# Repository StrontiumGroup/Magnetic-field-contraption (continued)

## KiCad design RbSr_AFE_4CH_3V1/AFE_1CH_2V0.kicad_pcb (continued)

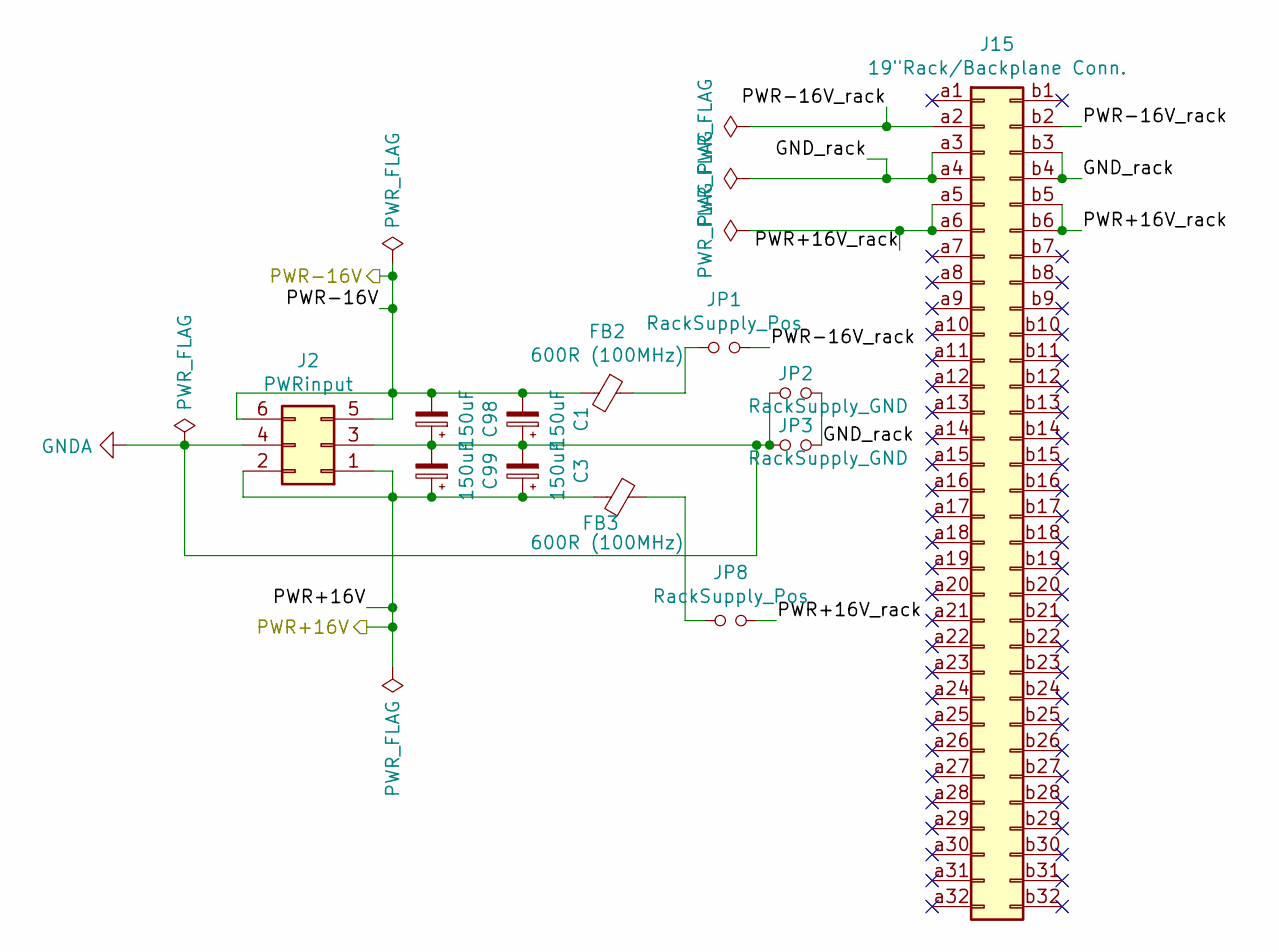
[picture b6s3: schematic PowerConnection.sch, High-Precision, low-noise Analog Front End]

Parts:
C1, C3, C98, C99: 150uF; CP_Elec_6.3x5.8; DigiKey 565-APXJ200ARA151MF61GCT-ND
FB2, FB3: 600R (100MHz); L_0603_1608Metric; DigiKey MH1608-601YCT-ND
J2: PWRinput; IDC-Header_2x03_P2.54mm_Vertical; DigiKey 609-5122-ND
J15: 19\"Rack/Backplane Conn.; Socket_DIN41612-CaseC1-AC-Male-64Pin-2rows; DigiKey 1195-1143-ND
JP1: RackSupply_Pos; PinHeader_1x02_P1.27mm_Vertical; DigiKey 732-5315-ND
JP2, JP3: RackSupply_GND; PinHeader_1x02_P1.27mm_Vertical; DigiKey 732-5315-ND
JP8: RackSupply_Pos; PinHeader_1x02_P1.27mm_Vertical; DigiKey 61300211121

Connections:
/PWR+16V: C3.1, C99.1, FB3.1, J2.1, J2.2; also elsewhere on the board
/PWR-16V: C1.2, C98.2, FB2.2, J2.5, J2.6; also elsewhere on the board
/PowerCconnection1/GND_rack: J15.a3, J15.a4, J15.b3, J15.b4, JP2.2, JP3.2
/PowerCconnection1/PWR+16V_rack: J15.a5, J15.a6, J15.b5, J15.b6, JP8.2
/PowerCconnection1/PWR-16V_rack: J15.a2, J15.b2, JP1.2
GND: C1.1, C3.2, C98.1, C99.2, J2.3, J2.4, JP2.1, JP3.1; also elsewhere on the board
unnamed: FB2.1, JP1.1
unnamed: FB3.2, JP8.1

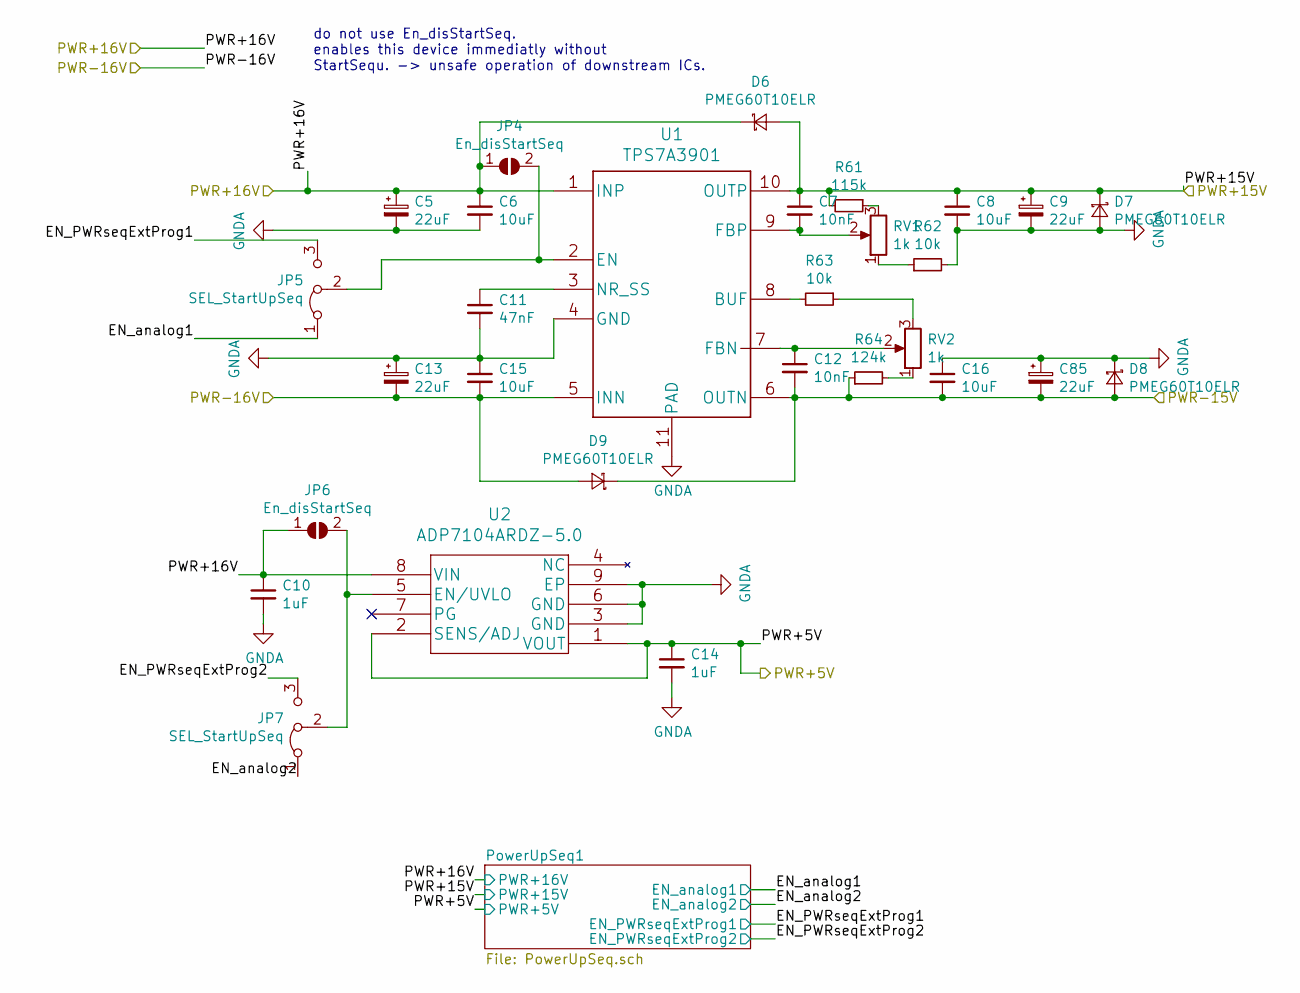
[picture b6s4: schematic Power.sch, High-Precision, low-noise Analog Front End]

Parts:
C5, C9, C13, C85: 22uF; CP_Elec_6.3x5.7; DigiKey 399-A767EB226M1VLAE050CT-ND
C6, C8, C15, C16: 10uF; C_1210_3225Metric; DigiKey 445-4536-1-ND
C7, C12: 10nF; R_0603_1608Metric; DigiKey 490-9666-1-ND
C10, C14: 1uF; C_0805_2012Metric; DigiKey 1276-1029-1-ND
C11: 47nF; C_0603_1608Metric; DigiKey 311-1427-1-ND
D6, D7, D8, D9: PMEG60T10ELR; D_SOD-123; DigiKey 1727-7807-1-ND
JP4, JP6: En_disStartSeq; SolderJumper-2_P1.3mm_Open_TrianglePad1.0x1.5mm
JP5, JP7: SEL_StartUpSeq; SolderJumper-3_P2.0mm_Open_TrianglePad1.0x1.5mm_NumberLabels
R61: 115k; R_0603_1608Metric; DigiKey 311-115KHRCT-ND
R62, R63: 10k; R_0805_2012Metric; DigiKey 311-10.0KCRCT-ND
R64: 124k; R_0603_1608Metric; DigiKey 311-124KHRCT-ND
RV1, RV2: 1k; Potentiometer_Bourns_3314G_Vertical; DigiKey 3314G-102ECT-ND
U1: TPS7A3901; Texas_DSC0010J_ThermalVias; DigiKey 296-47504-1-ND
U2: ADP7104ARDZ-5.0; SOIC-8-1EP_3.9x4.9mm_P1.27mm_EP2.41x3.81mm; DigiKey ADP7104ARDZ-5.0-R7CT-ND

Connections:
/PWR+5V: C14.1, U2.1 (VOUT), U2.2 (SENS/ADJ); also elsewhere on the board
/PWR+15V: C7.1, C8.1, C9.1, D6.2 (A), D7.1 (K), R61.2, U1.10 (OUTP); also elsewhere on the board
/PWR+16V: C5.1, C6.1, C10.1, D6.1 (K), JP4.1 (A), JP6.1 (A), U1.1 (INP), U2.8 (VIN); also elsewhere on the board
/PWR-15V: C12.2, C16.2, C85.2, D8.2 (A), D9.1 (K), R64.1, U1.6 (OUTN); also elsewhere on the board
/PWR-16V: C13.2, C15.2, D9.2 (A), U1.5 (INN); also elsewhere on the board
/Power/EN_PWRseqExtProg1: JP5.3 (B); also elsewhere on the board
/Power/EN_PWRseqExtProg2: JP7.3 (B); also elsewhere on the board
/Power/EN_analog1: JP5.1 (A); also elsewhere on the board
/Power/EN_analog2: JP7.1 (A); also elsewhere on the board
GND: C5.2, C6.2, C8.2, C9.2, C10.2, C11.2, C13.1, C14.2, C15.1, C16.1, C85.1, D7.2 (A), D8.1 (K), R62.2, U1.4 (GND), U1.11 (PAD), U2.3 (GND), U2.6 (GND), U2.9 (EP); also elsewhere on the board
unnamed: C7.2, RV1.2, U1.9 (FBP)
unnamed: C11.1, U1.3 (NR_SS)
unnamed: C12.1, RV2.2, U1.7 (FBN)
unnamed: JP4.2 (B), JP5.2 (C), U1.2 (EN)
unnamed: JP6.2 (B), JP7.2 (C), U2.5 (EN/UVLO)
unnamed: R61.1, RV1.3
unnamed: R62.1, RV1.1
unnamed: R63.1, RV2.3
unnamed: R63.2, U1.8 (BUF)
unnamed: R64.2, RV2.1

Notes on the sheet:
do not use En_disStartSeq. enables this device immediatly without StartSequ. -> unsafe operation of downstream ICs.

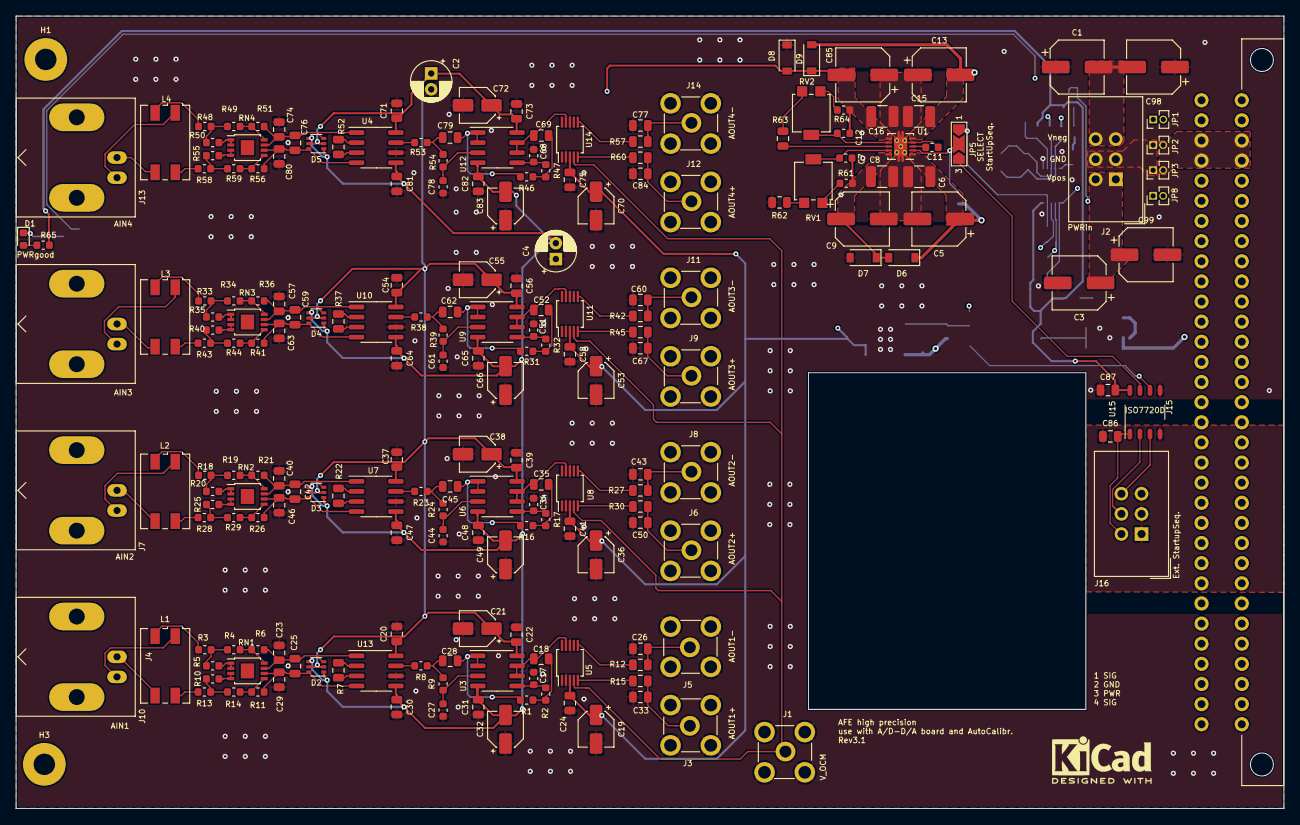
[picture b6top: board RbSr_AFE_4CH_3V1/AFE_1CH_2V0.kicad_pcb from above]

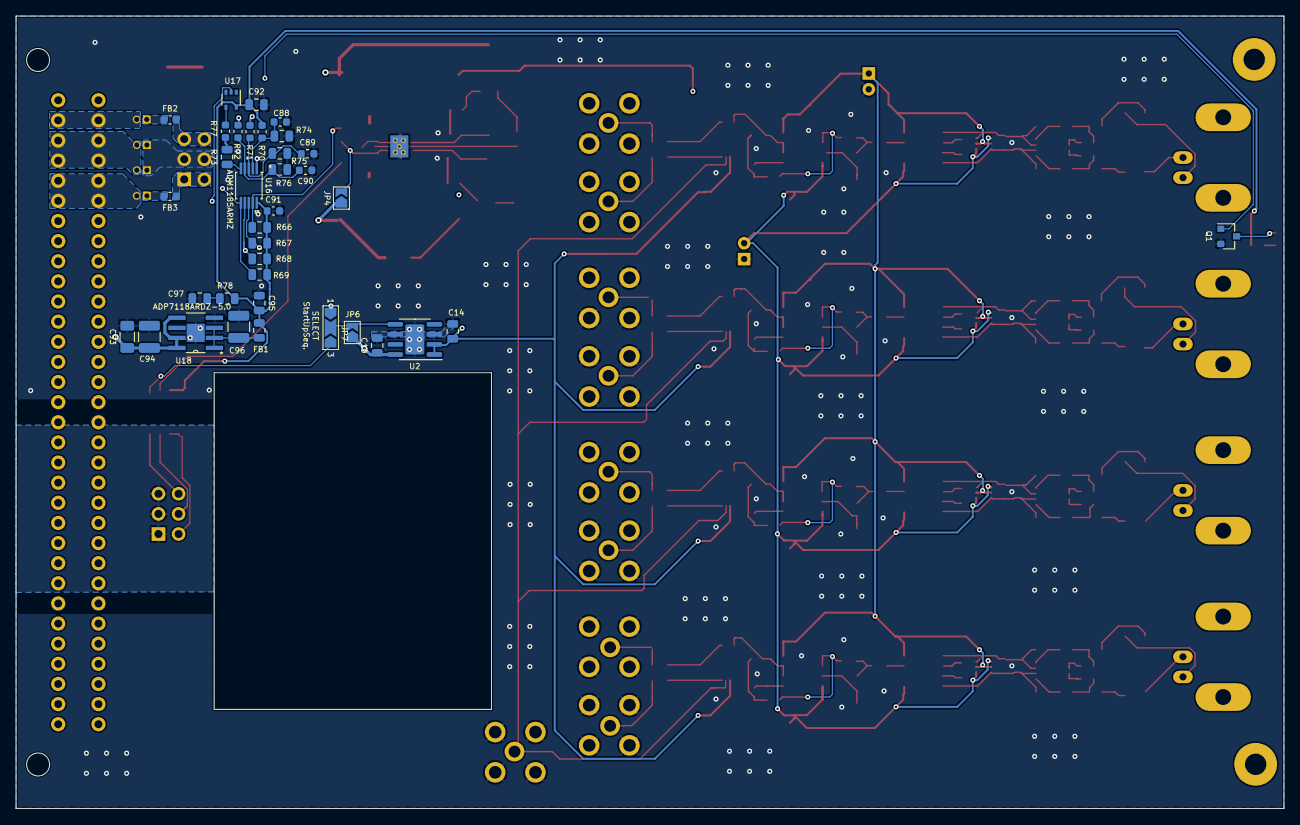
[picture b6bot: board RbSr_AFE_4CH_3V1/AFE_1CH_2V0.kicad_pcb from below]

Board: 4 copper layers, 160.0 x 100.0 mm, 244 parts (36 on the bottom side), 143 nets.

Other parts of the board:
C86, C87, C92, C95, C97: 100nF; C_0805_2012Metric
C88, C89, C90, C91: 1uF; C_0603_1608Metric
C93: 10uF; C_1206_3216Metric
C94, C96: 2.2uF; C_1210_3225Metric
D1: PWR_GD; LED_0603_1608Metric
FB1: 1k; L_0805_2012Metric
J16: Ext_PowerUpSeq; IDC-Header_2x03_P2.54mm_Vertical
Q1: 2N7002; SOT-23
R65: 1k; R_0603_1608Metric
R66, R67, R68, R69, R73, R74, R75, R76: 10k; R_0805_2012Metric
R70, R72, R77: 56k; R_0603_1608Metric
R71: 200k; R_0603_1608Metric
R78: 2R; R_0805_2012Metric
U15: ISO7720D; ISO7720
U16: ADM1185ARMZ; ADM1185ARMZ-1
U17: 74LVC1G17; SOT-353_SC-70-5
U18: ADP7118ARDZ-5.0; ADP7118

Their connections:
/PWR+5V: R72.2; also elsewhere on the board
/PWR+15V: R71.1; also elsewhere on the board
/PWR+16V: C93.1, C94.1, U18.5, U18.7, U18.8; also elsewhere on the board
/Power/EN_PWRseqExtProg1: U15.7; also elsewhere on the board
/Power/EN_PWRseqExtProg2: U15.6; also elsewhere on the board
/Power/EN_analog1: R66.2, U16.9; also elsewhere on the board
/Power/EN_analog2: R67.2, U16.8; also elsewhere on the board
/Power/PowerUpSeq1/EN_analog3: R68.2, U16.7, U17.2
/Power/PowerUpSeq1/PWR_GD: Q1.1, R69.2, U16.6
GND: C87.1, C88.2, C89.2, C90.2, C91.2, C92.2, C93.2, C94.2, C95.2, C96.2, C97.2, Q1.2, R74.2, R75.2, R76.2, U15.5, U16.1, U17.3, U18.4, U18.9; also elsewhere on the board
unnamed: C86.1, J16.1, J16.3, J16.5, U15.4
unnamed: C86.2, J16.2, U15.1
unnamed: C88.1, R70.1, R74.1, U16.2
unnamed: C89.1, R71.2, R75.1, U16.3
unnamed: C90.1, R72.1, R76.1, U16.4
unnamed: C96.1, FB1.1, U18.1, U18.2, U18.3
unnamed: C97.1, R78.2
unnamed: D1.1, Q1.3
unnamed: D1.2, R65.2
unnamed: J16.4, U15.2
unnamed: J16.6, U15.3
unnamed: R73.1, U16.5
unnamed: R73.2, R77.2
unnamed: R77.1, U17.4
VCC: C87.2, C91.1, C92.1, C95.1, FB1.2, R65.1, R66.1, R67.1, R68.1, R69.1, R70.2, R78.1, U15.8, U16.10, U17.5

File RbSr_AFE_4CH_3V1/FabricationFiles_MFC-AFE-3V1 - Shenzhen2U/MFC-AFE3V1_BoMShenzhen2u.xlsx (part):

|  |  |  |  |  | BOM & Assembly Template
 |  |  | INSTRUCTIONS: | 1. Please fill out all cells marked in blue
 |  |  |  | 2. Quote through Email: Send this Excel file along with your Gerber to: |  |  |  | pcba@shenzhen2u.com
 |  |  |  | Quote online: Upload this Excel file along with your Gerber on: |  |  |  | https://www.shenzhen2u.com/PCB-Assembly
 | Client Details
 | Client Information |  |  |  |  |  | Shipping Information
 | Company Name: |  | University of Amsterdam |  |  |  | Company Name: | University of Amsterdam
 | Client Name: |  | Lukas | Reichsöllner |  |  | Client Name: | Lukas
 | Address: |  | Science Park 904, C4.252 |  |  |  | Address: | Science Park 904, C4.252
 |  |  | Amsterdam 1098 XH |  |  |  |  | Amsterdam 1098 XH
 |  |  | Netherlands |  |  |  |  | Netherlands
 | Email: |  | l.reichsoellner@uva.nl |  |  |  | Email: | l.reichsoellner@uva.nl
 | Tel: |  |  |  |  |  | Tel: | 0
 | Project Details
 | Project Name |  |  | Quantity | Currency |  | Shipping Method |  | NOTE (N/A if not applicable)
 | MFC- AFE board Rev.3.0 |  |  | 4 | USD |  | DHL International
 | PCB Production
 | Material | Layer | X dimension (cm) | Y dimension (cm) | Thickness | Cooper | Solder Mask | Surface finish | Other requirment (N/A if not applicable)
 | FR4 | 4 | 16 | 10 | 1.6mm | 1 OZ | Green | HASL
 | PCBA Assembly
 | Qty of Unique Parts |  | Qty of SMT Parts | Qty of THT Parts | Qty of Leadless Parts (BGA, QFN, LCC) |  | Assembly Sides (single/double) |  | NOTE (N/A if not applicable)
 | 74 |  | 0 | 0 | 0 |  | Double |  | ROHS
 | BOM / Components Sourcing Detail
 | Note: For RCL Components, if you do not need any precise part number or manufac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
 | For non-chip components( buttons,connectors etc.),it is recommended to provide 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
 | NO. # | Part ID | Manufacturer | Part Number | Description | Reference Link | Value | Package | THT/SMT/No-Lead Pads | BOM Qty (pcs) | Total Qty (pcs)
 | 1 | C2 C4 | Würth Elektronik | 860240572002 | 22µF ±20% 35V Aluminum Electrolytic Radial Can 1.3Ohm@100kHz 5000 Hrs @ 105°C | https://octopart.com/860240572002-w%C3%BCrth+elektronik-53758684 | 22µF ±20% 35V Aluminum Electrolytic Radial Can 1.3Ohm@100kHz 5000 Hrs @ 105°C |  |  | 2 | 0
 | 2 | C25 C42 C59 C76 | Samsung | CL21B103JBANNNC | 10nF ±5% 50V MLCC X7R 0805 (2012 Metric) | https://octopart.com/cl21b103jbannnc-samsung-9302014 | 10nF ±5% 50V MLCC X7R 0805 (2012 Metric) |  |  | 4 | 0
 | 3 | C23 C29 C40 C46 C57 C63 C74 C80 | Samsung | CL21B102KBANNNC | 1nF ±10% 50V MLCC X7R 0805 (2012 Metric) | https://octopart.com/cl21b102kbannnc-samsung-9299369 | 1nF ±10% 50V MLCC X7R 0805 (2012 Metric) |  |  | 8 | 0
 | 4 | C20 C30 C26 C33 C24 C22 C31 C37 C47 C43 C50 C41 C39 C48 C54 C64 C60 C67 C58 C56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 | Würth Elektronik | 885012207098 | 0.1µF ±10% 50V Ceramic Capacitor X7R 0805 (2012 Metric) | https://octopart.com/885012207098-w%C3%BCrth+elektronik-65419869 | 0.1µF ±10% 50V Ceramic Capacitor X7R 0805 (2012 Metric) |  |  | 33 | 0
 | 5 | C19 C21 C32 C36 C38 C49 C53 C55 C66 C70 C72 C83 | KEMET | EEV106M035A9BAA | 10µF ±20% 35V Aluminum Electrolytic Radial Can 1.93Ohm@100kHz 2000 Hrs @ 105°C | https://octopart.com/eev106m035a9baa-kemet-22264518 | 10µF ±20% 35V Aluminum Electrolytic Radial Can 1.93Ohm@100kHz 2000 Hrs @ 105°C |  |  | 12 | 0
 | 6 | C28 C45 C62 C79 | TDK | C2012C0G1H333J125AA | 33nF ±5% 50V MLCC C0G NP0 0805 (2012 Metric) | https://octopart.com/c2012c0g1h333j125aa-tdk-26013652 | 33nF ±5% 50V MLCC C0G NP0 0805 (2012 Metric) |  |  | 4 | 0
 | 7 | C27 C44 C61 C78 | KEMET | C0603C362J5GACTU | 3.6nF ±5% 50V MLCC C0G NP0 0603 (1608 Metric) | https://octopart.com/c0603c362j5gactu-kemet-19050043 | 3.6nF ±5% 50V MLCC C0G NP0 0603 (1608 Metric) |  |  | 4 | 0
 | 8 | C18 C35 C52 C69 | KEMET | C0805C473J3GACTU | 47nF ±5% 25V MLCC C0G NP0 0805 (2012 Metric) | https://octopart.com/c0805c473j3gactu-kemet-9563153 | 47nF ±5% 25V MLCC C0G NP0 0805 (2012 Metric) |  |  | 4 | 0
 | 9 | C17 C34 C51 C68 | KEMET | C0603C472J3GACTU | 4.7nF ±5% 25V MLCC C0G NP0 0603 (1608 Metric) | https://octopart.com/c0603c472j3gactu-kemet-11705710 | 4.7nF ±5% 25V MLCC C0G NP0 0603 (1608 Metric) |  |  | 4 | 0
 | 10 | C1 C3 C98 C99 | United Chemi-Con | APXJ200ARA151MF61G | 150µF 20V Aluminum - Polymer Capacitors Radial Can - SMD 23mOhm 15000 Hrs @ 105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 | https://octopart.com/apxj200ara151mf61g-united+chemi-con-105791766 | 150µF 20V Aluminum - Polymer Capacitors Radial Can - SMD 23mOhm 15000 Hrs @ 105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 |  |  | 4 | 0
 | 11 | C12 C7 | Murata | GRM1885C1H103JA01D | 10000pF ±5% 50V Ceramic Capacitor C0G NP0 0603 (1608 Metric) | https://octopart.com/grm1885c1h103ja01d-murata-29183412 | 10000pF ±5% 50V Ceramic Capacitor C0G NP0 0603 (1608 Metric) |  |  | 2 | 0
 | 12 | C85 C9 C13 C5 | KEMET | A767EB226M1VLAE050 | 22µF 35V Aluminum - Polymer Capacitors Radial Can - SMD 50mOhm 2000 Hrs @ 105°C | https://octopart.com/a767eb226m1vlae050-kemet-75360436 | 22µF 35V Aluminum - Polymer Capacitors Radial Can - SMD 50mOhm 2000 Hrs @ 105°C |  |  | 4 | 0
 | 13 | C16 C8 C15 C6 | TDK | C3225X7S1H106K250AB | 10µF ±10% 50V Ceramic Capacitor X7S 1210 (3225 Metric) | https://octopart.com/c3225x7s1h106k250ab-tdk-25947885 | 10µF ±10% 50V Ceramic Capacitor X7S 1210 (3225 Metric) |  |  | 4 | 0
 | 14 | C11 | Yageo | CC0603KRX7R9BB473 | 0.047µF ±10% 50V Ceramic Capacitor X7R 0603 (1608 Metric) | https://octopart.com/cc0603krx7r9bb473-yageo-9292680 | 0.047µF ±10% 50V Ceramic Capacitor X7R 0603 (1608 Metric) |  |  | 1 | 0
 | 15 | C14 C10 | Samsung | CL21B105KBFNNNE | 1µF ±10% 50V MLCC X7R 0805 (2012 Metric) | https://octopart.com/cl21b105kbfnnne-samsung-10518888 | 1µF ±10% 50V MLCC X7R 0805 (2012 Metric) |  |  | 2 | 0
 | 16 | C91 C90 C88 C89 | Yageo | CC0603KRX5R9BB105 | 1µF ±10% 50V Ceramic Capacitor X5R 0603 (1608 Metric) | https://octopart.com/cc0603krx5r9bb105-yageo-48690813 | 1µF ±10% 50V Ceramic Capacitor X5R 0603 (1608 Metric) |  |  | 4 | 0
 | 17 | C94 C96 | TDK | C3225X7R2A225K230AM | 2.2µF ±10% 100V MLCC X7R 1210 (3225 Metric) | https://octopart.com/c3225x7r2a225k230am-tdk-25947876 | 2.2µF ±10% 100V MLCC X7R 1210 (3225 Metric) |  |  | 2 | 0
 | 18 | C93 | Samsung | CL31A106KBHNNNE | 10µF ±10% 50V MLCC X5R 1206 (3216 Metric) | https://octopart.com/cl31a106kbhnnne-samsung-19832778 | 10µF ±10% 50V MLCC X5R 1206 (3216 Metric) |  |  | 1 | 0
 | 19 | D2 D3 D4 D5 | Diodes Inc. | BAV199DW-7-F | Diode Array 2 Pair Series Connection Standard 85V 140mA (DC) Surface Mount 6-TS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 | https://octopart.com/bav199dw-7-f-diodes+inc.-326243 | Diode Array 2 Pair Series Connection Standard 85V 140mA (DC) Surface Mount 6-TS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 |  |  | 4 | 0
 | 20 | D6 D7 D8 D9 | Nexperia | PMEG60T10ELRX | Diode Schottky 60V 1A Surface Mount SOD-123W | https://octopart.com/pmeg60t10elrx-nexperia-89940781 | Diode Schottky 60V 1A Surface Mount SOD-123W |  |  | 4 | 0
 | 21 | D1 | Lite-On | LTST-S270KGKT | Green 571nm LED Indication - Discrete 2V 0603 (1608 Metric) | https://octopart.com/ltst-s270kgkt-lite-on-549938 | Green 571nm LED Indication - Discrete 2V 0603 (1608 Metric) |  |  | 1 | 0
 | 22 | FB2 FB3 | Bourns | MH1608-601Y | 600 Ohms @ 100MHz 1 Power Signal Line Ferrite Bead 0603 (1608 Metric) 1A 200mOhm | https://octopart.com/mh1608-601y-bourns-1717538 | 600 Ohms @ 100MHz 1 Power Signal Line Ferrite Bead 0603 (1608 Metric) 1A 200mOhm |  |  | 2 | 0
 | 23 | FB1 | TE Connectivity | BMB2A1000LN2 | 1 kOhms @ 100MHz 1 Ferrite Bead 0805 (2012 Metric) 350mA 300mOhm | https://octopart.com/bmb2a1000ln2-te+connectivity-7513312 | 1 kOhms @ 100MHz 1 Ferrite Bead 0805 (2012 Metric) 350mA 300mOhm |  |  | 1 | 0
 | 24 | H3 H1 |  |  | Mounting Hole |  | Mounting Hole |  |  | 2 | 0
 | 25 | J1 | TE Connectivity | 1-1337482-0 | SMB Connector Jack Male Pin 50Ohm Through Hole Solder | https://octopart.com/1-1337482-0-te+connectivity-40017790 | SMB Connector Jack Male Pin 50Ohm Through Hole Solder |  |  | 1 | 0
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
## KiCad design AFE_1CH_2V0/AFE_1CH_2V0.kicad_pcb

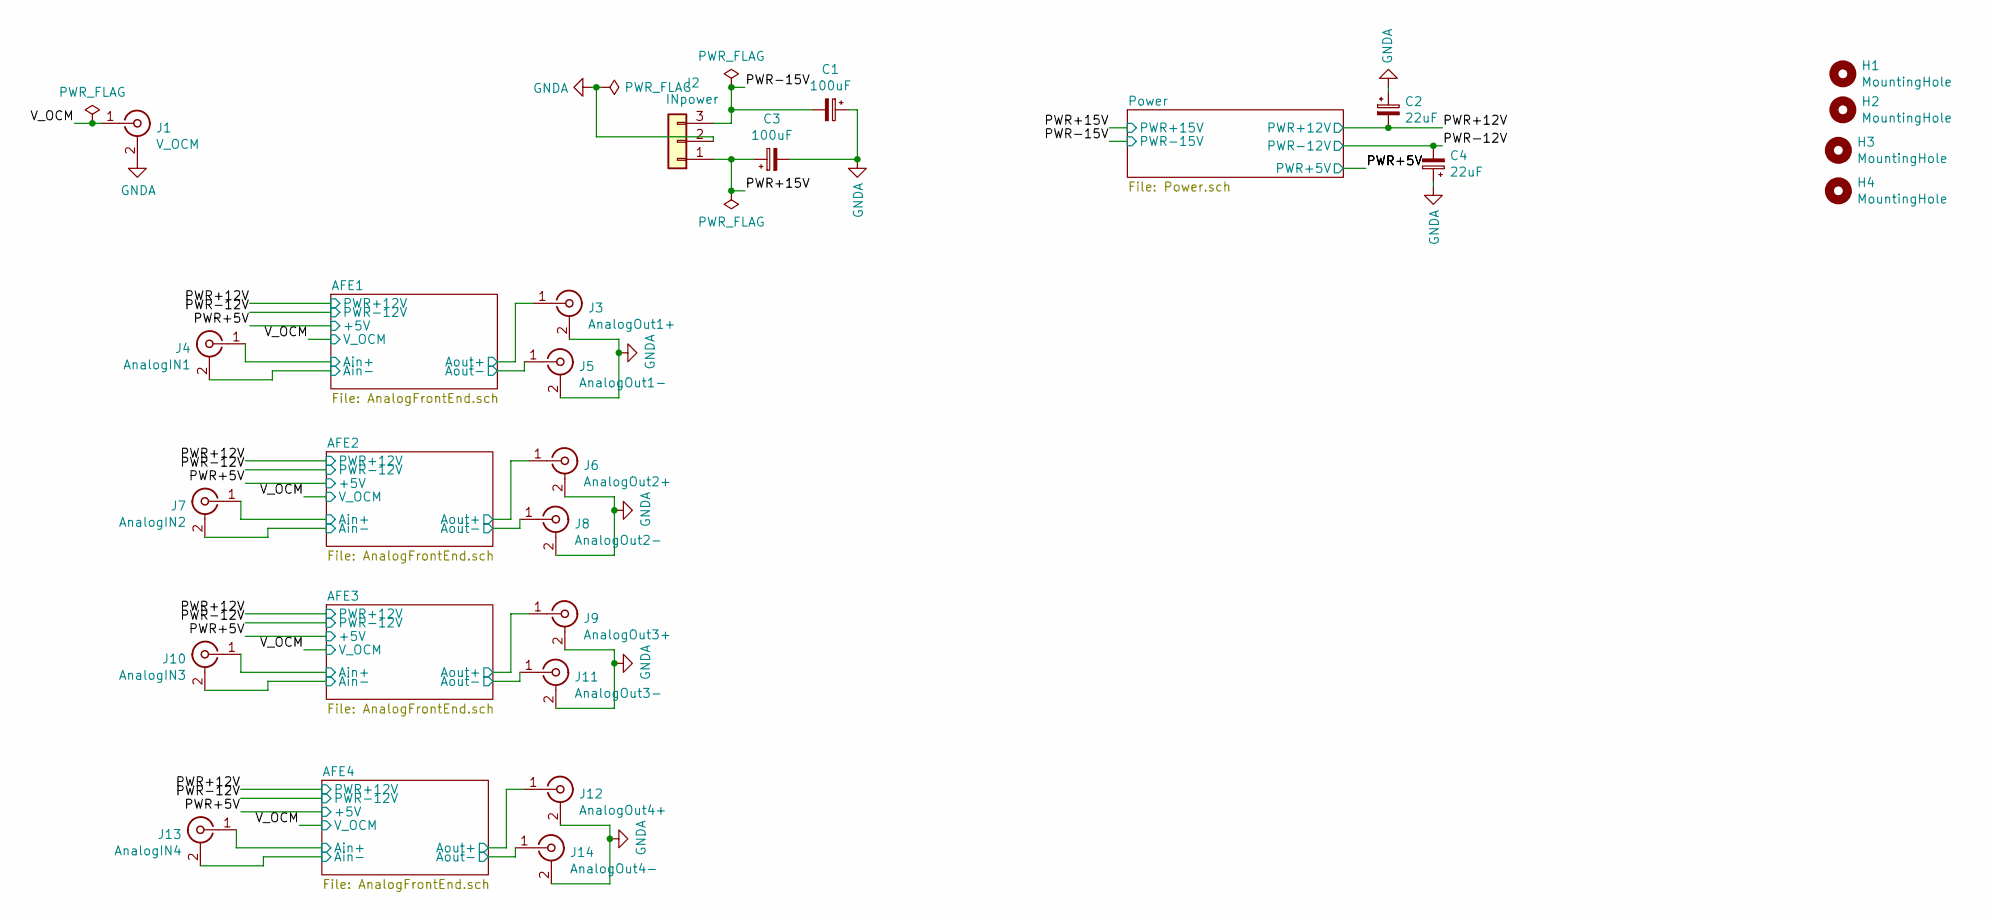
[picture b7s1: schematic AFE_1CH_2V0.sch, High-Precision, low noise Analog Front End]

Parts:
C1, C3: 100uF; CP_Radial_D6.3mm_P2.50mm; DigiKey 732-9170-1-ND
C2, C4: 22uF; CP_Radial_D5.0mm_P2.00mm; DigiKey 732-9317-1-ND
H1, H2, H3, H4: MountingHole; MountingHole_3.2mm_M3_Pad
J1: V_OCM; RF_SMB_jack_Vertical; DigiKey A102025-ND
J2: INpower; Molex_KK-254_AE-6410-03A_1x03_P2.54mm_Vertical; DigiKey WM19538-ND
J3: AnalogOut1+; RF_SMB_jack_Vertical; DigiKey A102025-ND
J4: AnalogIN1; BNC_Amphenol_B6252HB-NPP3G-50_Horizontal; DigiKey A97555-ND
J5: AnalogOut1-; RF_SMB_jack_Vertical; DigiKey A102025-ND
J6: AnalogOut2+; RF_SMB_jack_Vertical; DigiKey A102025-ND
J7: AnalogIN2; BNC_Amphenol_B6252HB-NPP3G-50_Horizontal; DigiKey A97555-ND
J8: AnalogOut2-; RF_SMB_jack_Vertical; DigiKey A102025-ND
J9: AnalogOut3+; RF_SMB_jack_Vertical; DigiKey A102025-ND
J10: AnalogIN3; BNC_Amphenol_B6252HB-NPP3G-50_Horizontal; DigiKey A97555-ND
J11: AnalogOut3-; RF_SMB_jack_Vertical; DigiKey A102025-ND
J12: AnalogOut4+; RF_SMB_jack_Vertical; DigiKey A102025-ND
J13: AnalogIN4; BNC_Amphenol_B6252HB-NPP3G-50_Horizontal; DigiKey A97555-ND
J14: AnalogOut4-; RF_SMB_jack_Vertical; DigiKey A102025-ND

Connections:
/AFE1/Ain+: J4.1 (In); also elsewhere on the board
/AFE1/Ain-: J4.2 (Ext); also elsewhere on the board
/AFE1/Aout+: J3.1 (In); also elsewhere on the board
/AFE1/Aout-: J5.1 (In); also elsewhere on the board
/AFE2/Ain+: J7.1 (In); also elsewhere on the board
/AFE2/Ain-: J7.2 (Ext); also elsewhere on the board
/AFE2/Aout+: J6.1 (In); also elsewhere on the board
/AFE2/Aout-: J8.1 (In); also elsewhere on the board
/AFE3/Ain+: J10.1 (In); also elsewhere on the board
/AFE3/Ain-: J10.2 (Ext); also elsewhere on the board
/AFE3/Aout+: J9.1 (In); also elsewhere on the board
/AFE3/Aout-: J11.1 (In); also elsewhere on the board
/AFE4/Ain+: J13.1 (In); also elsewhere on the board
/AFE4/Ain-: J13.2 (Ext); also elsewhere on the board
/AFE4/Aout+: J12.1 (In); also elsewhere on the board
/AFE4/Aout-: J14.1 (In); also elsewhere on the board
/PWR+12V: C2.2; also elsewhere on the board
/PWR+15V: C3.1, J2.1; also elsewhere on the board
/PWR-12V: C4.2; also elsewhere on the board
/PWR-15V: C1.2, J2.3; also elsewhere on the board
/V_OCM: J1.1 (In); also elsewhere on the board
GNDA: C1.1, C2.1, C3.2, C4.1, J1.2 (Ext), J2.2, J3.2 (Ext), J5.2 (Ext), J6.2 (Ext), J8.2 (Ext), J9.2 (Ext), J11.2 (Ext), J12.2 (Ext), J14.2 (Ext); also elsewhere on the board

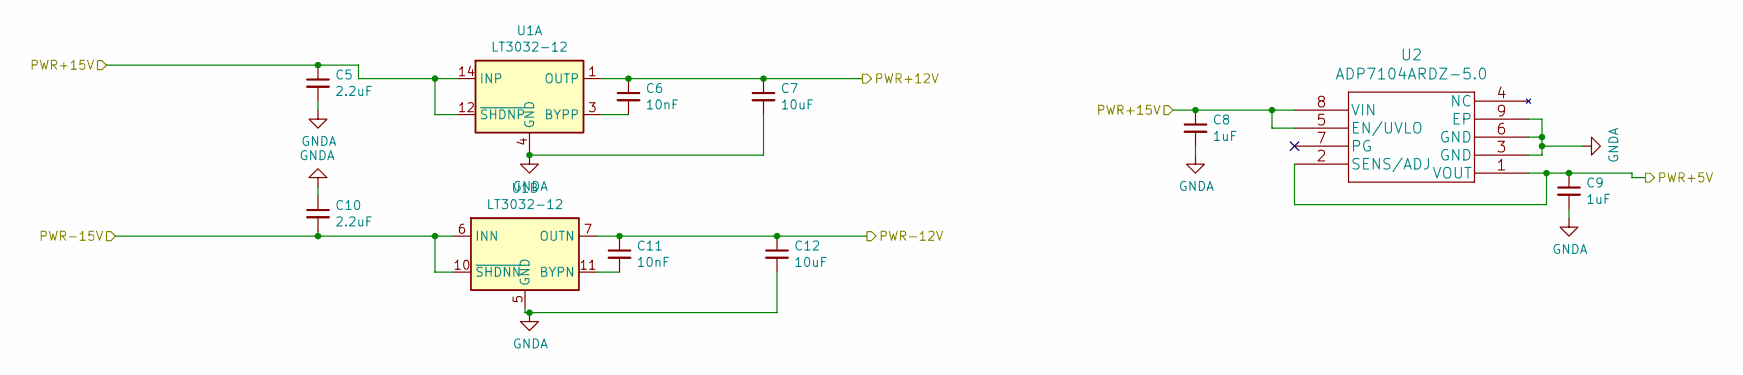
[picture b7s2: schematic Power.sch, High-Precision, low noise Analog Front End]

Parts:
C5, C10: 2.2uF; C_0805_2012Metric; DigiKey 478-5719-1-ND
C6, C11: 10nF; C_0603_1608Metric; DigiKey 445-15925-1-ND
C7, C12: 10uF; C_1210_3225Metric; DigiKey 445-1434-1-ND
C8, C9: 1uF; C_0805_2012Metric; DigiKey 1276-1029-1-ND
U1: LT3032-12; Linear_DE14MA
U2: ADP7104ARDZ-5.0; SOIC-8-1EP_3.9x4.9mm_P1.27mm_EP2.41x3.81mm_ThermalVias; DigiKey ADP7104ARDZ-5.0-R7CT-ND

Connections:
/PWR+5V: C9.1, U2.1 (VOUT), U2.2 (SENS/ADJ); also elsewhere on the board
/PWR+12V: C6.1, C7.1, U1.1 (OUTP); also elsewhere on the board
/PWR+15V: C5.1, C8.1, U1.12 (~SHDNP), U1.14 (INP), U2.5 (EN/UVLO), U2.8 (VIN); also elsewhere on the board
/PWR-12V: C11.1, C12.1, U1.7 (OUTN); also elsewhere on the board
/PWR-15V: C10.2, U1.6 (INN), U1.9 (INN), U1.10 (~SHDNN); also elsewhere on the board
GNDA: C5.2, C7.2, C8.2, C9.2, C10.1, C12.2, U1.4 (GND), U1.5 (GND), U2.3 (GND), U2.6 (GND), U2.9 (EP); also elsewhere on the board
unnamed: C6.2, U1.3 (BYPP)
unnamed: C11.2, U1.11 (BYPN)
